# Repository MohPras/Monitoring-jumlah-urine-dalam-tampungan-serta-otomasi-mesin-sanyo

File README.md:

# Monitoring-jumlah-urine-dalam-tampungan-serta-otomasi-mesin-sanyo/pomba-air

Project ini adalah project smart farm, Dalam instalasi kadang management urine sangat penting karena apabila urine dari domba di biarkan secara terbuka dalam jumlah yang banyak maka akan menimbulkan hal buruk bagi lingkungan serta kesehatan domba tersebut, maka dari itu alat monitoring jumlah urine dalam tampungan ini dibuat agar kita bisa melakukan management urine dengan baik dimana fungsi monitroing ini untuk mengetahui sudah berapa liter urine domba yang masuk ke tampungan untuk selanjutnya apabila sudah penuh maka akan disedot ke tampungan selanjutnya dengan sanyo yang di otomasisasi.

Cara kerja alat ini adalah pertama sensor proximity bekerja untuk melakukan perhitungan sudah berapa liter urine dalam tampungan jika sudah penuh maka proximity akan mengirimkan sinyal ke relay supaya relay aktif dan melakukan triger ke pompa air outputnya urine akan tersedot hingga habis. RTC bekerja sebagai timer dimana dalam penyedotan urine dibutuhkan waktu 2 menit untuk sampai habis maka dari itu RTC berfungsi sebagai patokan waktu supaya motor hanya hidup selama 2 menit saja.

Berikut adalah design pcb dari rangkaian monitoring urine serta otomasisasi pompa air

Dalam pembuatan alat ini ada bahan-bahan yang digunakan yaitu:
- Sensor Proximity yang berfungsi untuk mengtahui volume urine dalam tampungan
- Pompa air untuk melakukan penyedotan urine secara otomatis
- Relay berfungsi sebagai saklar otomatis
- RTC berfungsi sebagai timer dalam pengoprasian alat ini
- LCD untuk display

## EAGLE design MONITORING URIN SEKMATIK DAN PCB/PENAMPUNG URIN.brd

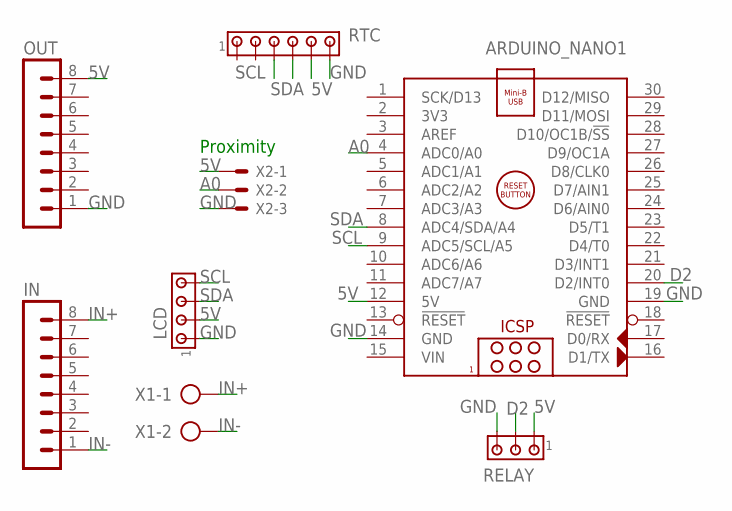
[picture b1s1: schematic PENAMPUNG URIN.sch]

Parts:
ARDUINO_NANO1: ARDUINO_NANO
IN: MA08-1
LCD: MTA04-100; 10X04MTA
OUT: MA08-1
RELAY: MTA03-100; 10X03MTA
RTC: MTA06-100; 10X06MTA
X1: AK500/2-H
X2: KK-156-3

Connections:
5V: ARDUINO_NANO1.12 (5V), LCD.2, OUT.8, RELAY.1, RTC.5, X2.1
A0: ARDUINO_NANO1.4 (ADC0/A0), X2.2
D2: ARDUINO_NANO1.20 (D2/INT0), RELAY.2
GND: ARDUINO_NANO1.14 (GND), ARDUINO_NANO1.19 (GND), LCD.1, OUT.1, RELAY.3, RTC.6, X2.3
IN+: IN.8, X1.1
IN-: IN.1, X1.2
SCL: ARDUINO_NANO1.9 (ADC5/SCL/A5), LCD.4, RTC.3
SDA: ARDUINO_NANO1.8 (ADC4/SDA/A4), LCD.3, RTC.4
VIN: ARDUINO_NANO1.15 (VIN)

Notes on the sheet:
Proximity

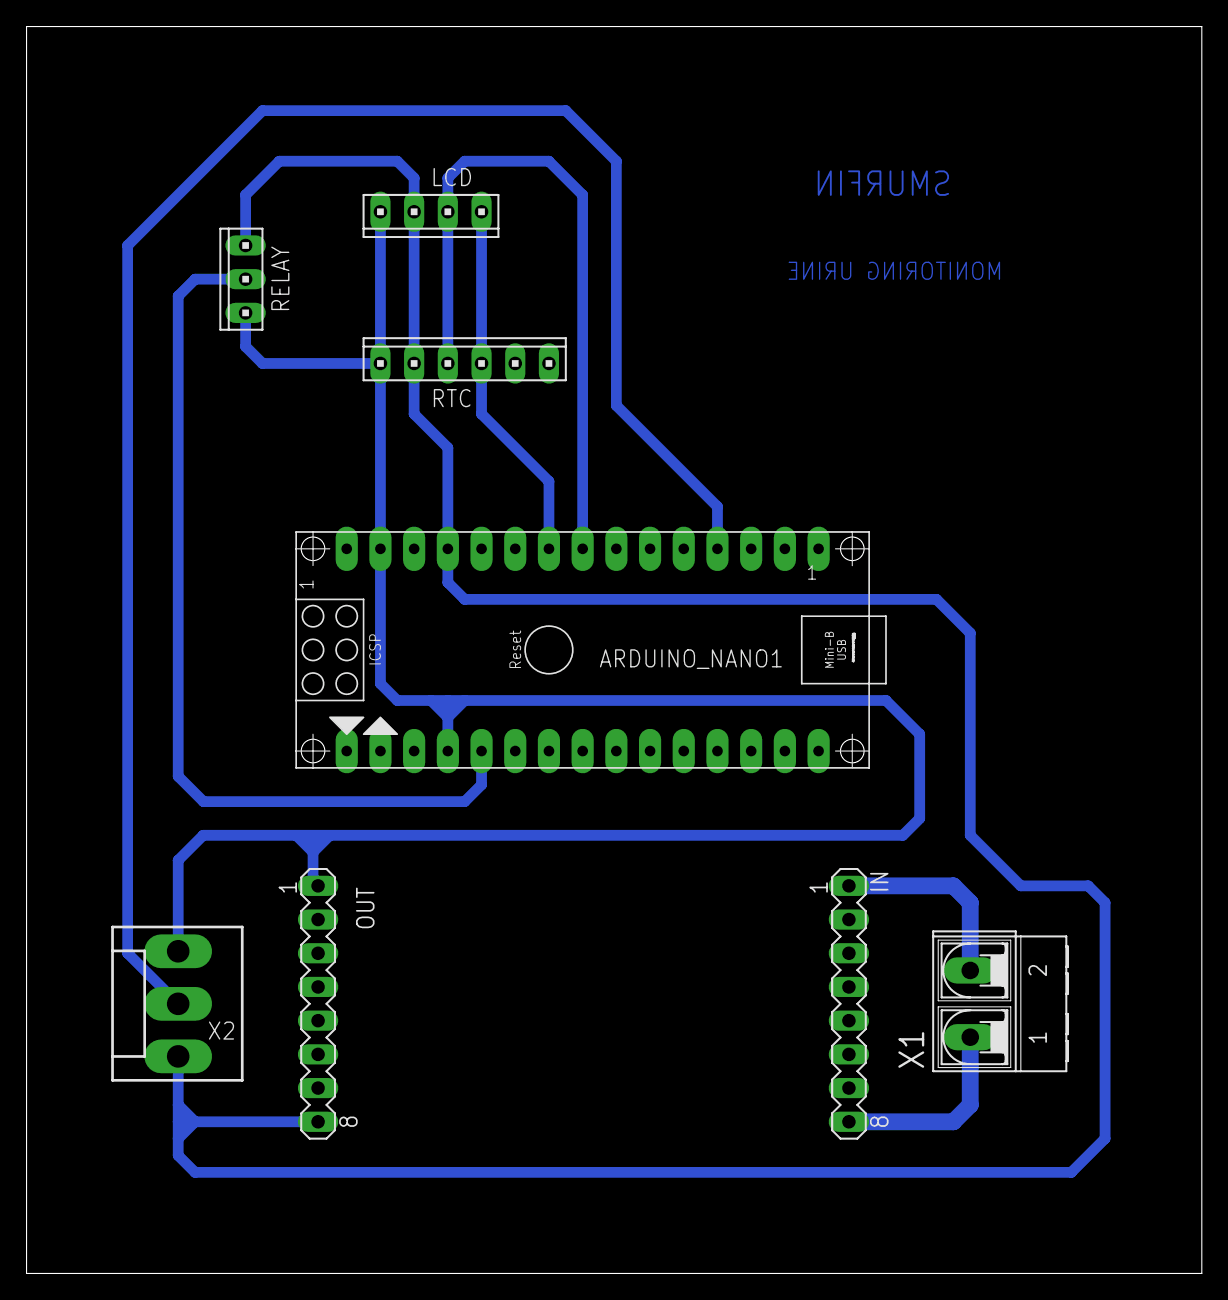
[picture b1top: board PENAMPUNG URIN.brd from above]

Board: 2 copper layers, 88.6 x 94.0 mm, 8 parts (0 on the bottom side), 8 nets.
